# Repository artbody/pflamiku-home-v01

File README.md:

# pflamiku-home-v01
automated home watering system for plants
This system is Arduino micro plus based.

You need:

one Arduino micro plus 5V16 

one  LM298N Motor Driver Breakout board

one LED

two simple switches

two Resistors 1 kOhm

one Resistor 220 Ohm

a few cables and connectors

two waterpumps

4 metalplates 1 by 2 inch as capacitive sensors ( this could also be a pcb)

That's it

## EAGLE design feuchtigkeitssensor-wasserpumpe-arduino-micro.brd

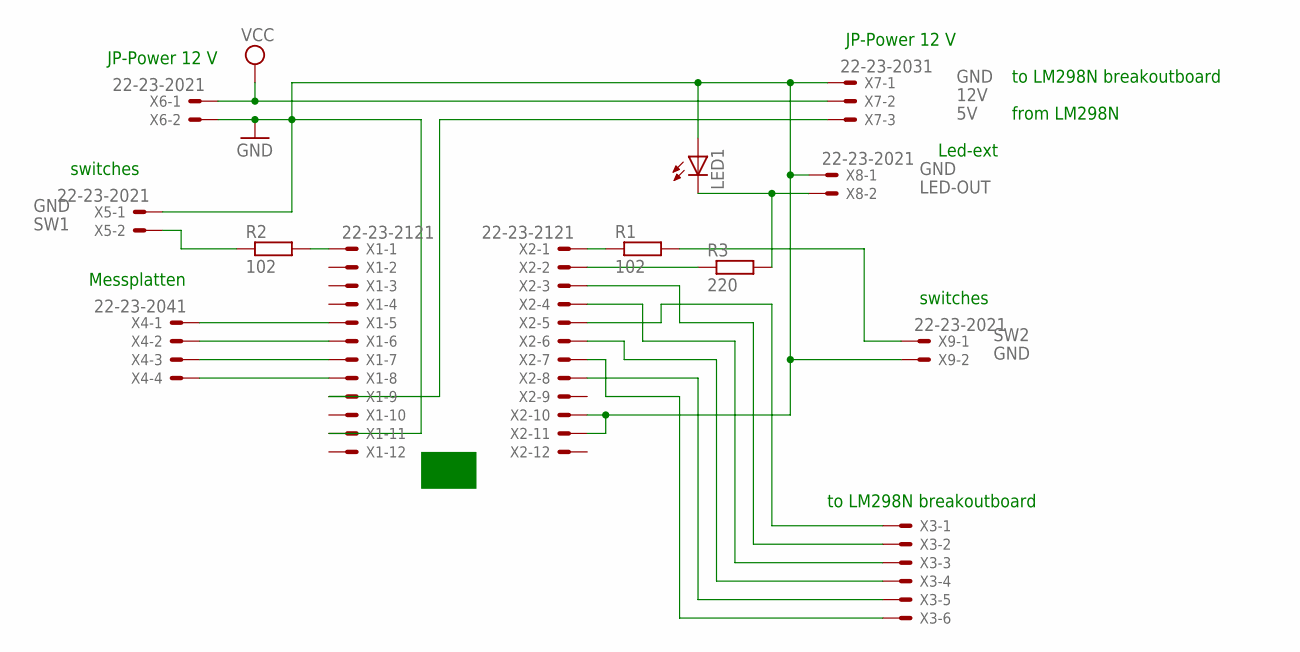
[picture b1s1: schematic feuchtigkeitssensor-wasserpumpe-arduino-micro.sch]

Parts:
LED1: LED5MM
R1, R2: 102; M1206
R3: 220; M1206
X1, X2: 22-23-2121
X3: 22-23-2061
X4: 22-23-2041
X5, X6, X8, X9: 22-23-2021
X7: 22-23-2031

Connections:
5V: X1.9, X7.3
12V: X6.1, X7.2
GND: LED1.A, X1.11, X2.10, X2.11, X5.1, X6.2, X7.1, X8.1, X9.2
LED-OUT: LED1.K (C), R3.2, X8.2
unnamed: X1.8, X4.4
unnamed: X1.7, X4.3
unnamed: X1.6, X4.2
unnamed: X1.5, X4.1
unnamed: R2.2, X1.1
unnamed: R1.1, X2.1
unnamed: R3.1, X2.2
unnamed: X2.5, X3.1
unnamed: X2.3, X3.2
unnamed: X2.4, X3.3
unnamed: X2.7, X3.6
unnamed: X2.8, X3.5
unnamed: X2.6, X3.4
SW1: R2.1, X5.2
SW2: R1.2, X9.1

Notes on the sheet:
JP-Power 12 V
Messplatten
switches
Led-ext
to LM298N breakoutboard
from LM298N

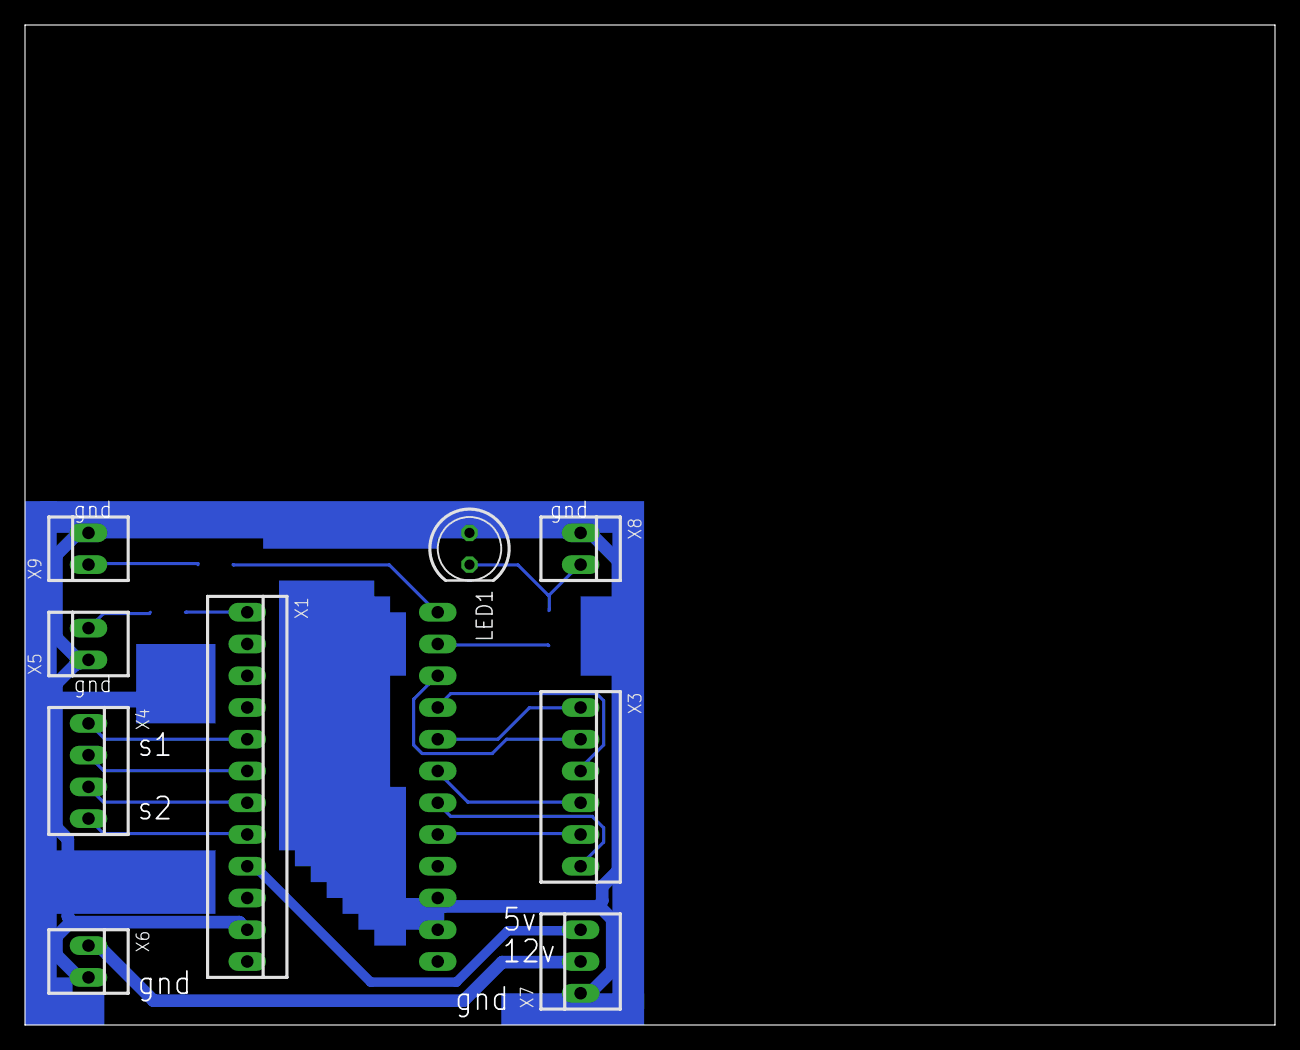
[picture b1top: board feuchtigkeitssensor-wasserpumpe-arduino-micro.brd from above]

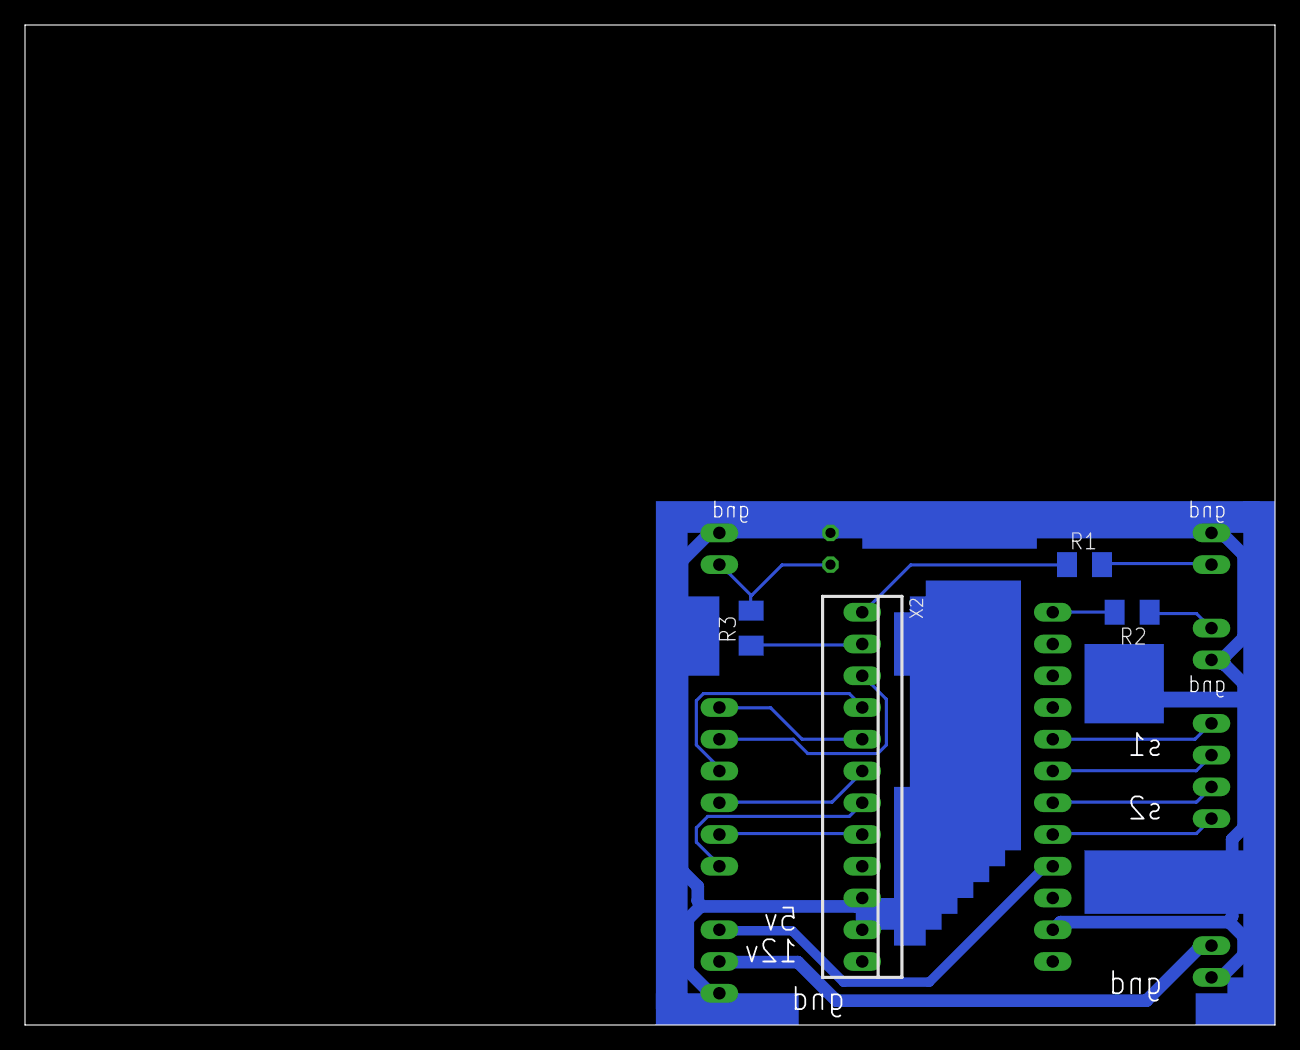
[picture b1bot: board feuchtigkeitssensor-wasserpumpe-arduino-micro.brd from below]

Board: 2 copper layers, 100.0 x 80.0 mm, 13 parts (4 on the bottom side), 19 nets.

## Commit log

2017-07-17 Add files via upload
    Entwicklungsboard Bild hinzugefügt
2017-07-17 Add files via upload
    Version 1 (development)
    you need arduino ide 1.8.3 and one arduino micro pro 5v16
